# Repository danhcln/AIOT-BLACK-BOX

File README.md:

# AIoT Smart Black Box for Electric Motorcycles

> **Tên đề tài**: Thiết kế hộp đen AIoT thông minh phân tích và ghi lại sự cố xe máy điện  
> **Tác giả**: Nguyễn Lê Công Danh (danhcln)  
> **Ngành**: Kỹ thuật Điện - Điện tử / IoT & Hệ thống nhúng  
> **Nền tảng vi điều khiển**: Espressif ESP32-S3 (N16R8)  
> **Công cụ thiết kế EDA**: KiCad v8 / v9  
> **Trạng thái phần cứng**: Đã hoàn thiện thiết kế mạch in PCB 1 lớp đồng `B.Cu` (Nghiệm thu GATE 3.2 - 0 lỗi ERC/DRC)

---

## 1. Giới thiệu dự án (Project Introduction)

Hộp đen AIoT (Event Data Recorder - EDR) cho xe máy điện là một thiết bị thông minh gắn trên phương tiện hai bánh nhằm liên tục giám sát trạng thái động học, phát hiện các tình huống tai nạn, va chạm, đổ ngã và tự động gửi cảnh báo khẩn cấp (kèm tọa độ định vị GPS toàn cầu) về người thân/cứu hộ thông qua mạng viễn thông 4G LTE.

Đồng thời, toàn bộ dữ liệu cảm biến (gia tốc 3 trục, vận tốc góc, vận tốc di chuyển, thời gian thực và trạng thái hệ thống) được ghi liên tục với tần số cao vào thẻ nhớ MicroSD theo định dạng hộp đen tiêu chuẩn, phục vụ công tác điều tra nguyên nhân tai nạn và phân tích hành vi lái xe.

```
+---------------------------------------------------------------------------------------------------+
|                                 HỆ THỐNG HỘP ĐEN AIoT XE MÁY ĐIỆN                                 |
+---------------------------------------------------------------------------------------------------+
|  [CẢM BIẾN & ĐỘNG HỌC]    [ĐỊNH VỊ & VIỄN THÔNG]     [LƯU TRỮ & HIỂN THỊ]    [NGUỒN & AN TOÀN]    |
|   - MPU6050 (Gia tốc/Góc)  - NEO-M8N (GPS/GNSS)       - MicroSD (SPI Logger)  - UPS LX-2BUPS (5V) |
|   - DS3231 (Thời gian RTC) - A7680C (4G LTE / SMS)    - OLED 0.96" (SSD1306)  - Pin 18650 Li-ion  |
|                                                                               - Còi 5V & Nút Hủy  |
+---------------------------------------------------------------------------------------------------+
                                                  |
                                                  v
                               +-------------------------------------+
                               |   VI ĐIỀU KHIỂN TRUNG TÂM ESP32-S3  |
                               |    Dual-Core Xtensa LX7 @ 240MHz    |
                               |    16MB Flash + 8MB Octal PSRAM     |
                               +-------------------------------------+
```

---

## 2. Mục tiêu hệ thống (System Objectives)

1. **Giám sát động học thời gian thực**: Đo lường gia tốc 3 trục ($A_x, A_y, A_z$) và vận tốc góc ($\omega_x, \omega_y, \omega_z$) để phát hiện tức thời trạng thái ngã xe (nghiêng $> 60^\circ$) hoặc va chạm mạnh ($> 3G$).
2. **Định vị toàn cầu chính xác**: Cập nhật tọa độ kinh độ, vĩ độ, độ cao và tốc độ di chuyển từ vệ tinh GPS/GLONASS với chu kỳ 10Hz.
3. **Cảnh báo cứu nạn tự động qua SMS 4G**: Khi xảy ra sự cố, hệ thống đếm ngược 10 giây (kèm còi báo động). Nếu người lái không bấm nút hủy (CANCEL), hệ thống lập tức soạn tin nhắn SMS chứa link Google Maps chính xác gửi tới số điện thoại khẩn cấp.
4. **Ghi nhật ký hộp đen liên tục**: Lưu trữ dữ liệu cảm biến dạng CSV vào thẻ nhớ MicroSD (chu kỳ 100ms/mẫu) với nhãn thời gian thực chính xác đến từng giây từ RTC DS3231.
5. **Giao diện trực quan**: Hiển thị tốc độ xe, trạng thái kết nối GPS, sóng 4G, góc nghiêng và thời gian thực trên màn hình OLED 0.96 inch.
6. **Nguồn điện độc lập, tin cậy**: Sử dụng mạch quản lý sạc/xả thông minh UPS 2 cell 18650, tự động duy trì hoạt động khi ắc quy chính của xe bị ngắt nguồn do va chạm.
7. **Thiết kế phần cứng tối ưu chi phí**: Bo mạch Carrier Board được thiết kế hoàn hảo trên **PCB 1 lớp đồng `B.Cu`**, sử dụng các jumper dây cách điện chuẩn hóa, dễ dàng gia công và hàn thủ công trong điều kiện phòng thí nghiệm tại Việt Nam.

---

## 3. Sơ đồ khối tổng quan (System Architecture)

```
                       +-----------------------------+
                       |   Ắc quy xe / Nguồn USB-C   |
                       +-----------------------------+
                                      |
                                      v
                       +-----------------------------+
                       |    MẠCH NGUỒN LX-2BUPS      |
                       |  (Pin 18650 + Sạc + Boost)  |
                       +-----------------------------+
                                      |
                                      +------------------+
                                      | 5V_SYS (Tải 3A)   |
                                      v                  v
                             +-----------------+  +-----------------+
                             | BUCK MINI-360   |  |   A7680C 4G     |
                             | (5V -> 3V3_SYS) |  | (Đỉnh dòng 2A)  |
                             +-----------------+  +-----------------+
                                      |
       +------------------------------+------------------------------+
       |                              |                              |
       v                              v                              v
+---------------+             +---------------+             +-----------------+
| MPU-6050      |             | DS3231 RTC    |             | OLED 0.96"      |
| I2C: 0x69     |             | I2C: 0x68     |             | I2C: 0x3C       |
+---------------+             +---------------+             +-----------------+
       |                              |                              |
       +------------------------------+------------------------------+
                                      |
                                  Bus I2C (SDA: GPIO8 | SCL: GPIO9)
                                      |
                                      v
                       +-----------------------------+
                       |   ESP32-S3 DEVKITC-1 N16R8  |
                       +-----------------------------+
                        |      |        |          |
      Bus SPI (MOSI:11  |      |        |          |
               MISO:13  |      |        |          | UART (TX:17 | RX:18)
               SCK:12   |      |        |          +---------------------> NEO-M8N GPS
               CS:10)   |      |        |
                        v      |        | UART (TX:16 | RX:15)
                 MicroSD Card  |        +---------------------> SIM A7680C 4G
                               |
                               +------------------------------> Nút CANCEL (GPIO6)
                               |
                               +------------------------------> Còi báo (GPIO5) & LED (GPIO7)
```

---

## 4. Các linh kiện chính & Bảng bóc tách vật tư (BOM)

Toàn bộ các linh kiện trong hệ thống đã được kiểm toán thực tế và khóa mã trong bảng bóc tách vật tư [`BOM_MAINBOARD_REV1.csv`](./PCB_AIOT_BLACKBOX/AIOT_BLACKBOX_MAINBOARD_REV1/BOM_MAINBOARD_REV1.csv):

| TT | Ký hiệu (RefDes) | Tên linh kiện / Module | Thông số kỹ thuật | Giao tiếp / Chân ESP32-S3 | Ghi chú & Vai trò |
|---|---|---|---|---|---|
| 1 | **U1** | ESP32-S3-DevKitC-1 N16R8 | Dual-Core 240MHz, 16MB Flash, 8MB PSRAM | Bo mạch trung tâm | Điều khiển toàn bộ hệ thống |
| 2 | **U2** | MPU-6050 (GY-521) | Con quay hồi chuyển & Gia tốc kế 6-DOF | I2C (SDA: 8, SCL: 9) | Chân AD0 nối 3V3 $\rightarrow$ Địa chỉ `0x69` |
| 3 | **U3** | DS3231 (ZS-042) | Real-Time Clock có bù nhiệt độ TCXO | I2C (SDA: 8, SCL: 9) | Địa chỉ `0x68` (Đã gỡ bỏ trở sạc R5) |
| 4 | **U4** | NEO-M8N GNSS Module | 72 kênh định vị đa vệ tinh (GPS/GLONASS) | UART (TX: 17, RX: 18) | Baudrate 9600 bps, chu kỳ 10Hz |
| 5 | **U5** | A7680C 4G LTE Breakout | LTE Cat-1 hỗ trợ SMS, TCP/IP, VoLTE | UART (TX: 16, RX: 15) | Baudrate 115200 bps, cấp nguồn hình sao |
| 6 | **J1** | MicroSD Card Adapter | Chuẩn SPI có đệm logic và IC ổn áp 3.3V | SPI (CS: 10, MOSI: 11, SCK: 12, MISO: 13) | Định dạng FAT32, ghi log sự cố liên tục |
| 7 | **U7** | OLED 0.96 inch | 128x64 điểm ảnh, Driver SSD1306 | I2C (SDA: 8, SCL: 9) | Địa chỉ `0x3C`, hiển thị trạng thái |
| 8 | **U6** | Module Buck 3.3V (Mini-360) | Hạ áp xung DC-DC 5V $\rightarrow$ 3.3V / 2A | Nguồn hệ thống | Cung cấp nguồn riêng `3V3_SYS` |
| 9 | **J2** | Module UPS LX-2BUPS | Mạch sạc/xả dự phòng 2 cell 18650, ra 5V/3A | Nguồn tổng `5V_SYS` | Cấp nguồn chính không gián đoạn |
| 10 | **BZ1** | Còi báo chủ động (Active Buzzer) | 5V Piezoelectric Audio Indicator | Điều khiển qua Q1 (GPIO5) | Kêu cảnh báo trước khi phát tín hiệu SOS |
| 11 | **SW1** | Nút bấm hủy cảnh báo (CANCEL) | Nút nhấn nhả THT kèm tụ chống dội 100nF | GPIO6 (Kéo lên $10\text{k}\Omega$) | Hủy phát SMS khẩn cấp trong 10 giây |
| 12 | **D1** | LED báo trạng thái 5mm | LED siêu sáng màu xanh lá kèm trở $330\Omega$ | GPIO7 | Nhấp nháy báo hệ thống hoạt động |
| 13 | **NT1** | Net-Tie hình sao nguồn SIM | Đường đồng liền `B.Cu` rộng 2.5mm | Nối `5V_SYS` $\rightarrow$ `SIM_PWR` | Ngăn sụt áp lan truyền khi phát sóng 4G |
| 14 | **JMP1..11**| 11 Wire Jumper mặt trên | Dây đồng 22/24 AWG bọc cách điện Teflon/PVC | Cắm xuyên lỗ xuống `B.Cu` | Xử lý các đường giao cắt trên PCB 1 lớp |

---

## 5. ESP32-S3 và Firmware (`filecodemain.cpp`)

Toàn bộ logic hoạt động được lập trình tối ưu trong file firmware duy nhất: [`filecodemain.cpp`](./filecodemain.cpp).

### Bản đồ phân bổ chân phần cứng (GPIO Mapping Locked)
```cpp
// 1. I2C Bus (OLED, RTC DS3231, IMU MPU6050)
#define I2C_SDA_PIN         8
#define I2C_SCL_PIN         9

// 2. SPI Bus (MicroSD Card Adapter)
#define SD_CS_PIN          10
#define SPI_MOSI_PIN       11
#define SPI_SCK_PIN        12
#define SPI_MISO_PIN       13

// 3. UART Hardware (Module 4G LTE A7680C)
#define SIM_TX_PIN         16   // ESP32 TX -> SIM RX
#define SIM_RX_PIN         15   // ESP32 RX -> SIM TX

// 4. UART Hardware (Module GPS NEO-M8N)
#define GPS_TX_PIN         17   // ESP32 TX -> GPS RX
#define GPS_RX_PIN         18   // ESP32 RX -> GPS TX

// 5. Điều khiển ngoại vi và an toàn
#define BUZZER_PIN          5   // Điều khiển cực Base transistor Q1
#define CANCEL_BTN_PIN      6   // Nút bấm hủy gửi SMS (kéo lên nội trở + R3)
#define LED_STATUS_PIN      7   // LED nhấp nháy chỉ báo trạng thái
```

### Thuật toán vận hành cốt lõi
1. **Khởi tạo (Setup)**:
   - Khởi tạo cổng nạp Serial (115200 bps).
   - Thiết lập I2C Bus tại tần số chuẩn 100kHz.
   - Quét bus I2C và khởi tạo OLED (`0x3C`), DS3231 (`0x68`), MPU6050 (`0x69`).
   - Cấu hình dải đo MPU6050 $\pm 16G$, bộ lọc thông thấp số $21\text{Hz}$.
   - Khởi tạo SPI và mount phân vùng thẻ nhớ MicroSD. Tạo file nhật ký `blackbox_YYYYMMDD.csv` nếu chưa có.
   - Khởi động UART1 (GPS) và UART2 (SIM 4G). Đồng bộ tập lệnh AT cho module SIM.
2. **Vòng lặp chính (Loop - Non-blocking State Machine)**:
   - **Tần số 10Hz (100ms)**: Đọc dữ liệu gia tốc và góc nghiêng từ MPU6050; đọc câu tin NMEA từ GPS. Ghi một dòng log vào thẻ nhớ:
     `Timestamp, AccX, AccY, AccZ, GyroX, GyroY, GyroZ, Lat, Lon, Speed, Status`
   - **Xử lý tai nạn**: Nếu góc nghiêng $|Angle| > 60^\circ$ hoặc $|Acc| > 3.0G$, hệ thống chuyển sang trạng thái `ACCIDENT_TRIGGERED`.
   - **Đếm ngược cứu hộ**: Bật còi BZ1 kêu bíp liên tục trong 10 giây. Nếu trong thời gian này người lái bấm nút CANCEL (GPIO6), hệ thống hủy lệnh và quay về bình thường.
   - **Gửi tin nhắn SOS**: Hết 10 giây, module A7680C kích hoạt lệnh `AT+CMGS`, gửi tin nhắn SMS chứa link Google Maps:
     `[EDR VI TRI XE] https://maps.google.com/?q=<Latitude>,<Longitude>`
   - **Cập nhật màn hình OLED (500ms)**: Hiển thị tọa độ, tốc độ, dung lượng thẻ nhớ và trạng thái kết nối.

> **Lưu ý bảo mật**: Trong bản chia sẻ công khai trên GitHub, số điện thoại khẩn cấp `DEFAULT_PHONE` được thay bằng giá trị placeholder `09xxxxxxxx`. Người triển khai thực tế chỉ cần thay bằng số điện thoại của người thân.

---

## 6. MPU6050 – Phát hiện chuyển động bất thường

- **Địa chỉ phần cứng I2C**: Được khóa cứng ở mức `0x69` bằng cách cấp nguồn `3V3_SYS` vào chân **AD0** (thông qua jumper `JMP8`). Điều này ngăn ngừa hoàn toàn hiện tượng xung đột địa chỉ với RTC DS3231 (`0x68`).
- **Xử lý tín hiệu**: Firmware sử dụng bộ lọc số thông thấp DLPF $21\text{Hz}$ để triệt tiêu dao động rung cơ học từ mặt đường và động cơ xe máy điện, chỉ bắt các xung gia tốc thực của va chạm.
- **Quy chuẩn bố trí trên PCB**: Module MPU6050 được đặt tại tâm trọng lực bo mạch (Zone 4), cách xa còi báo động tối thiểu 40mm để chống nhiễu sóng âm và từ trường.

---

## 7. GPS NEO-M8N – Định vị toàn cầu

- **Độ nhạy & Băng tần**: Hỗ trợ đồng thời hệ thống định vị GPS của Mỹ và GLONASS của Nga. Tốc độ cập nhật 10Hz, độ chính xác vị trí $< 2.5\text{m}$.
- **Bảo toàn tín hiệu**: Giao tiếp qua UART phần cứng (GPIO17 / GPIO18) với baudrate 9600 bps. Pin dự phòng trên module giúp duy trì dữ liệu ephemeris vệ tinh (Hot Start $< 1\text{s}$).

---

## 8. SIM A7680C – Viễn thông 4G LTE & Gửi SMS

- **Băng tần mạng**: Hỗ trợ 4G LTE Cat-1 (B1/B3/B5/B8/B34/B38/B39/B40/B41) tương thích hoàn toàn với tất cả nhà mạng tại Việt Nam (Viettel, Vinaphone, Mobifone).
- **Chống sụt áp phát sóng**: Module 4G tiêu thụ dòng đỉnh lên tới $2\text{A}$ trong thời gian ngắn (xung phát RF 577µs). Mạch in được trang bị nhánh nguồn hình sao `SIM_PWR` rộng 2.5mm đi qua Net-Tie `NT1` cùng cặp tụ lọc Low-ESR $470\mu\text{F}$ và $100\text{nF}$ đặt sát chân cấp nguồn module.

---

## 9. RTC DS3231 – Thời gian thực chính xác cao

- **Độ chính xác**: Sử dụng thạch anh tích hợp có bù nhiệt độ (TCXO), sai số cực thấp $< \pm 2\text{ppm}$ ($< 1$ phút mỗi năm).
- **An toàn pin**: Đã gỡ bỏ điện trở sạc R5 trên module ZS-042 để sử dụng an toàn với pin cúc áo thông thường CR2032 không sạc, loại bỏ triệt để nguy cơ phồng nổ pin.

---

## 10. MicroSD – Ghi dữ liệu hộp đen

- Giao tiếp qua bus SPI tốc độ cao. Dữ liệu được ghi theo khối nhị phân và đóng gói định dạng CSV tiêu chuẩn.
- Tự động kiểm tra tính toàn vẹn của thẻ nhớ khi khởi động; chỉ thị cảnh báo lỗi lên OLED nếu thẻ chưa được cắm hoặc hỏng định dạng.

---

## 11. OLED 0.96 inch – Màn hình hiển thị

- Sử dụng màn hình OLED công nghệ SSD1306 độ phân giải 128x64 điểm ảnh, giao tiếp I2C 2 dây.
- Hiển thị trực quan tốc độ di chuyển hiện tại, số lượng vệ tinh GPS kết nối, trạng thái sóng 4G, góc nghiêng thời gian thực và thời gian ngày/giờ.

---

## 12. Khối nguồn thông minh UPS LX-2BUPS

- **Nguồn cấp chính**: 2 cell pin Lithium-ion 18650 mắc song song, tích hợp IC quản lý sạc/xả thông minh và mạch boost DC-DC đồng bộ cho ra điện áp ổn định $5\text{V} / 3\text{A}$ (`5V_SYS`).
- **Nguồn sạc ngoài**: Cổng USB-C / VBUS hỗ trợ sạc điện tự động khi cắm sạc ngoài.
- **Nguồn thứ cấp**: Module Buck xung Mini-360 hạ áp từ `5V_SYS` xuống `3V3_SYS` cấp riêng cho khối logic cảm biến, tuyệt đối không dùng nguồn từ chân 3.3V của ESP32 để nuôi ngoại vi.

---

## 13. Bản vẽ Schematic KiCad

Hệ thống được thiết kế hoàn chỉnh trên KiCad EDA với đầy đủ các dự án nguyên lý:
1. **Schematic hệ thống chính**: Nằm tại [`PCB_AIOT_BLACKBOX/AIOT_BLACKBOX_MAINBOARD_REV1/AIOT_BLACKBOX_MAINBOARD_REV1.kicad_sch`](./PCB_AIOT_BLACKBOX/AIOT_BLACKBOX_MAINBOARD_REV1/AIOT_BLACKBOX_MAINBOARD_REV1.kicad_sch).
2. **Schematic báo cáo & thuyết minh chuẩn A4 Landscape**: Nằm tại [`Schematic_Thay/AIOT_BLACKBOX_PRESENTATION/AIOT_BLACKBOX_PRESENTATION.kicad_sch`](./Schematic_Thay/AIOT_BLACKBOX_PRESENTATION/AIOT_BLACKBOX_PRESENTATION.kicad_sch).
3. **Schematic chuyên sâu khối nguồn**: Nằm tại [`THIET_KE_KHOI_NGUON/AIOT_BLACKBOX_POWER_SUPPLY.kicad_sch`](./THIET_KE_KHOI_NGUON/AIOT_BLACKBOX_POWER_SUPPLY.kicad_sch).

---

## 14. Thiết kế PCB một lớp đồng `B.Cu` & 11 Wire Jumper

Nhằm phục vụ chế tạo thủ công trong phòng thí nghiệm (phương pháp ủi phim nhiệt, rửa mạch hóa chất $\text{FeCl}_3$ hoặc phay cơ CNC PCB 1 mặt), bo mạch được thiết kế theo các nguyên tắc nghiêm ngặt:
- **Chỉ 1 lớp đồng dẫn điện**: Toàn bộ đường mạch đồng, pad hàn và mặt phẳng mass GND đều nằm độc quyền trên lớp đáy **`B.Cu`**.
- **Không sử dụng Via**: Tuyệt đối không có via xuyên bo, loại bỏ hoàn toàn công đoạn gia công mạ lỗ phức tạp.
- **Giải quyết giao cắt bằng 11 Jumper dây cách điện**: Các đường tín hiệu logic bị giao cắt được xử lý bằng 11 cầu nhảy dây đồng lõi đơn (Teflon/PVC) cắm mặt trên (`Top`) và hàn vào các pad THT chuyên dụng.

### Bảng thông số kỹ thuật 11 Jumper dây (REV3)
| Jumper | Pitch (mm) | Net kết nối | Vai trò kỹ thuật |
|---|---|---|---|
| **`JMP1`** | 12.70 mm | `Net-(J1-MOSI)` | Nhảy tín hiệu SPI MOSI qua SCK và MISO vào ESP32 Pin 17 |
| **`JMP2`** | 7.62 mm | `3V3_SYS` | Nhảy nguồn 3V3_SYS qua đường SIM_PWR (2.5mm) cấp R3 nút bấm |
| **`JMP3`** | 7.62 mm | `Net-(U1-GPIO6)` | Nhảy tín hiệu CANCEL qua chân Base Q1 còi báo động vào ESP32 Pin 6 |
| **`JMP4`** | 10.16 mm | `/I2C_SDA_GPIO8` | Nhảy bus dữ liệu I2C_SDA qua đường ngang SCL (Y=91.50) |
| **`JMP5`** | 7.62 mm | `Net-(U1-GPIO6)` | Nhảy tín hiệu CANCEL qua xương nguồn 5V_SYS (Y=43.50) |
| **`JMP6`** | 10.16 mm | `Net-(J1-MISO)` | Nhảy tín hiệu SPI MISO qua chân 5V và GND của header MicroSD J1 |
| **`JMP7`** | 10.16 mm | `3V3_SYS` | Nhảy nguồn 3V3_SYS qua SCL cấp cho RTC DS3231 và IMU MPU6050 |
| **`JMP8`** | 12.70 mm | `3V3_SYS` | Nhảy 3V3_SYS cấp AD0 MPU6050 để khóa cứng địa chỉ I2C `0x69` |
| **`JMP9`** | 7.62 mm | `3V3_SYS` | Nhảy 3V3_SYS cấp trở kéo lên R_PU2 ($4.7\text{k}\Omega$) cho bus SCL |
| **`JMP10`** | 7.62 mm | `/I2C_SCL_GPIO9` | Nhảy xung I2C_SCL qua sống ngang SDA (Y=104.00) cấp màn hình OLED |
| **`JMP11`** | 12.70 mm | `GND` | Nhảy mass GND MicroSD J1.6 qua sống 5V_SYS vào mặt phẳng mass GND |

---

## 15. Hình ảnh phần cứng & Bản vẽ PCB (Gallery)

Các bản vẽ độ phân giải cao 300 DPI phục vụ chế tạo và lắp ráp được lưu trữ tại thư mục [`PCB_AIOT_BLACKBOX/AIOT_BLACKBOX_MAINBOARD_REV1/GATE_3_ROUTING/`](./PCB_AIOT_BLACKBOX/AIOT_BLACKBOX_MAINBOARD_REV1/GATE_3_ROUTING/):

- **Bản vẽ mặt đồng đáy (B.Cu Mirrored)**: [`PCB_ROUTING_BOTTOM_COPPER_ONLY_REV3.png`](./PCB_AIOT_BLACKBOX/AIOT_BLACKBOX_MAINBOARD_REV1/GATE_3_ROUTING/PCB_ROUTING_BOTTOM_COPPER_ONLY_REV3.png) – Bản vẽ soi gương sẵn sàng in phim rửa mạch.
- **Bản vẽ lắp ráp & Jumper mặt trên (Top Assembly)**: [`PCB_ROUTING_TOP_JUMPERS_REV3.png`](./PCB_AIOT_BLACKBOX/AIOT_BLACKBOX_MAINBOARD_REV1/GATE_3_ROUTING/PCB_ROUTING_TOP_JUMPERS_REV3.png) – Hướng dẫn chi tiết vị trí và màu sắc dây jumper.
- **Bản vẽ bố trí linh kiện tổng thể (Top Placement)**: [`PCB_PLACEMENT_TOP_REV2.png`](./PCB_AIOT_BLACKBOX/AIOT_BLACKBOX_MAINBOARD_REV1/GATE_2_PLACEMENT/PCB_PLACEMENT_TOP_REV2.png).
- **Hình ảnh linh kiện module thực tế**: Lưu trữ trong thư mục [`Hình ảnh linh kiện/`](./Hình%20ảnh%20linh%20kiện/).

---

## 16. Cấu trúc thư mục Repository & Hướng dẫn tra cứu (Navigation Guide)

```
AIOT-BLACK-BOX/
├── .agents/                                # Quy tắc thiết kế và skill của hệ thống Antigravity
│   ├── rules/                              # PCB_DESIGN_RULES_AIOT.md và quy tắc an toàn
│   └── skills/                             # Các công cụ kiểm toán, xác minh và sửa lỗi
├── Bao_Cao/                                # Báo cáo đồ án định dạng Word (.docx) và PDF
├── DATASHEET_LINH_KIEN/                    # Chỉ mục tra cứu thông số kỹ thuật và link chính hãng
│   ├── DATASHEET_INDEX.csv                 # Bảng tra cứu CSV 30 tài liệu sản xuất
│   ├── DATASHEET_INDEX.xlsx                # Bảng tính Excel định dạng màu
│   └── README.md                           # Hướng dẫn và link tải trực tiếp từ nhà sản xuất
├── Hình ảnh linh kiện/                     # Thư viện ảnh chụp thực tế hai mặt của các module
├── Mẫu của thầy/                           # Biểu mẫu, nhật ký và sơ đồ khối mẫu từ giảng viên
├── PCB_AIOT_BLACKBOX/                      # Dự án thiết kế mạch in PCB KiCad
│   └── AIOT_BLACKBOX_MAINBOARD_REV1/       # Project PCB chính thức của hệ thống
│       ├── AIOT_Blackbox_Local.pretty/     # Thư viện Footprint KiCad nội bộ dự án
│       ├── BOM_MAINBOARD_REV1.csv          # Bảng bóc tách vật tư 40 linh kiện (kèm 11 jumper)
│       ├── GATE_0_AUDIT/                   # Hồ sơ kiểm toán code, sơ đồ chân và công suất
│       ├── GATE_1_FOOTPRINT/               # Hồ sơ xác minh footprint và kích thước cơ khí
│       ├── GATE_2_PLACEMENT/               # Hồ sơ và hình ảnh định vị linh kiện chuẩn RF
│       ├── GATE_3_ROUTING/                 # Bản vẽ PCB hoàn thiện REV3 (Bottom & Top Jumpers)
│       ├── AIOT_BLACKBOX_MAINBOARD_REV1.kicad_pcb # File thiết kế mạch in KiCad PCB chính thức
│       ├── AIOT_BLACKBOX_MAINBOARD_REV1.kicad_sch # File nguyên lý kết nối bo mạch
│       └── fp-lib-table, sym-lib-table     # Cấu hình thư viện dự án
├── Schematic/                              # Thiết kế nguyên lý ban đầu
├── Schematic_Thay/                         # Thiết kế nguyên lý chuẩn hóa thuyết minh A4 Landscape
├── THIET_KE_KHOI_NGUON/                    # Dự án thiết kế và tính toán chi tiết khối nguồn
├── filecodemain.cpp                        # Firmware chính thức của ESP32-S3
├── SCHEMATIC_DRAWING_RULES.md              # Bộ quy chuẩn trình bày bản vẽ nguyên lý
├── BAO_GIA_LINH_KIEN_AIOT_SMART_BLACK_BOX.xlsx # Bảng báo giá linh kiện thị trường TP.HCM
├── .gitignore                              # Cấu hình loại bỏ file rác, file tạm và cache
└── README.md                               # Tài liệu giới thiệu tổng quan dự án (File này)
```

> **Lưu ý về thư viện KiCad**: Để đảm bảo tính độc lập và khả năng mở dự án trên mọi máy tính khác nhau mà không bị mất dấu thư viện, dự án sử dụng bảng ánh xạ thư viện cục bộ (`sym-lib-table` và `fp-lib-table`). Nếu mở trên máy mới, hãy giữ nguyên cấu trúc thư mục để KiCad tự động nhận diện biến môi trường `${KIPRJMOD}`.

---

## 17. Trạng thái phát triển hiện tại (Development Status)

- **Firmware**: Đã nạp và kiểm tra thành công trên phần cứng rời (ESP32-S3, OLED, MPU6050, DS3231, NEO-M8N, A7680C, MicroSD).
- **Schematic**: Đạt **0 Error, 0 Warning** khi chạy kiểm tra tự động `kicad-cli sch erc`.
- **PCB Carrier Board**: Đã hoàn thành nghiệm thu **GATE 3.2** trên bo mạch 1 lớp đồng `B.Cu` với 11 wire jumper, đạt **0 vi phạm chập mạch, 0 vi phạm khoảng cách cách điện, 0 vi phạm va chạm lỗ khoan và 0 đường dây giao cắt**.
- **Kế hoạch tiếp theo**: Tiến hành phân tích toàn vẹn nguồn điện tải nặng (GATE 4), chuẩn bị xuất Gerber và chế tạo mẫu thử nghiệm vật lý (GATE 5 & 6).

---

## 18. Các bước thử nghiệm & Hạn chế kỹ thuật (Testing & Limitations)

1. **Hạn chế của mạch in 1 lớp**: Việc sử dụng 11 wire jumper ở mặt trên là bắt buộc do định lý tô-pô mặt phẳng đối với các mạch có mật độ bus song song cao (I2C, SPI, UART). Người lắp ráp cần tuân thủ nghiêm ngặt bảng hướng dẫn chiều dài và cỡ dây trong file [`JUMPER_ASSEMBLY_REV3.csv`](./PCB_AIOT_BLACKBOX/AIOT_BLACKBOX_MAINBOARD_REV1/GATE_3_ROUTING/JUMPER_ASSEMBLY_REV3.csv).
2. **Yêu cầu đo kiểm trước khi cấp nguồn**: Do các lô linh kiện mua thực tế tại cửa hàng có thể có sự khác biệt về điện áp chân VCC của module SIM (3.8V hay 5V) hoặc thứ tự chân OLED (GND-VCC hay VCC-GND), bắt buộc phải dùng đồng hồ VOM đo kiểm tra thông mạch và điện áp tại các Test Point (`TP1`, `TP2`, `TP3`, `TP4`) trước khi cắm module vào socket.
3. **Môi trường hoạt động**: Thiết bị được thiết kế thử nghiệm trong môi trường xe máy điện tiêu chuẩn; khi đóng vỏ thực tế cần bổ sung đệm mút cao su chống sốc quanh cảm biến MPU6050 để giảm thiểu tối đa hiện tượng báo động giả do rung xóc cơ học.

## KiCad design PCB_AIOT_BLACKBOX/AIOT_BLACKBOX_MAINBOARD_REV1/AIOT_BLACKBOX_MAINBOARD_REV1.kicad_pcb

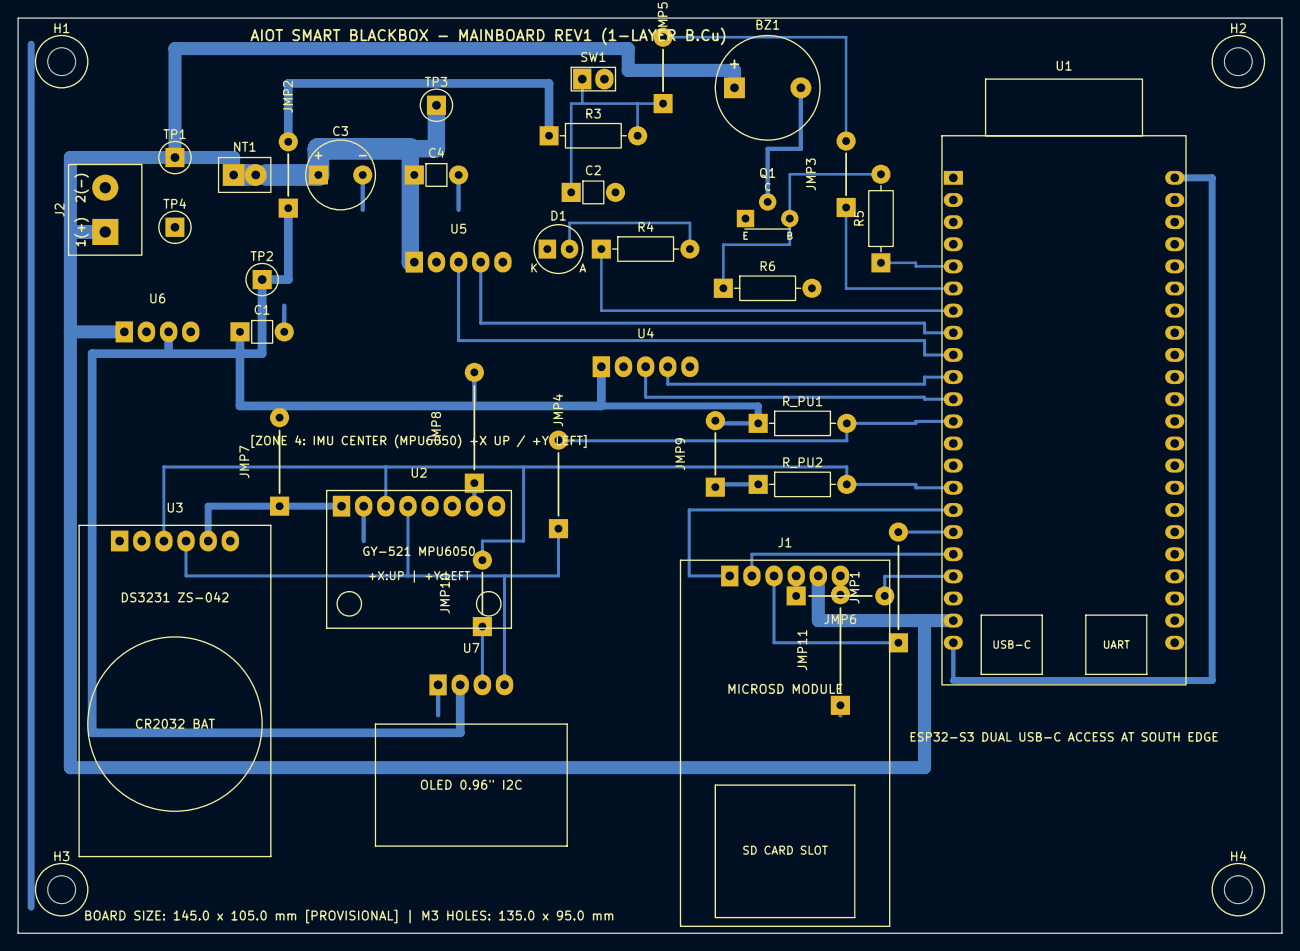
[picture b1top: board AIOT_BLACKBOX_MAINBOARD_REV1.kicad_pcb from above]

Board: 2 copper layers, 145.0 x 105.0 mm, 43 parts (0 on the bottom side), 20 nets.

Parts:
BZ1: BUZZER; Buzzer_D12.0mm_P7.62mm_SingleLayer
C1, C2, C4: 100nF; C_Disc_D5.0mm_P5.08mm_SingleLayer
C3: 470uF; CP_Radial_D8.0mm_P5.08mm_SingleLayer
D1: LED; LED_D5.0mm_P2.54mm_SingleLayer
H1, H2, H3, H4: M3_NPTH_PROVISIONAL; MountingHole_3.2mm_M3_NPTH
J1: MICROSD; Module_MicroSD_Adapter_1x06_P2.54mm_SingleLayer
J2: LX-2BUPS_5V_3A; TermBlock_1x02_P5.08mm_SingleLayer
JMP1, JMP8, JMP11: Wire_Jumper_12.70mm; WireJumper_P12.70mm_SingleLayer
JMP2, JMP3, JMP5, JMP9, JMP10: Wire_Jumper_7.62mm; WireJumper_P7.62mm_SingleLayer
JMP4, JMP6, JMP7: Wire_Jumper_10.16mm; WireJumper_P10.16mm_SingleLayer
NT1: STAR_5V_TO_SIM_PWR; NetTie_2_StarPoint_BCu_Width2.5mm
Q1: 2SC1815; TO-92_2SC1815_ECB_Staggered_SingleLayer
R3, R6: 10k; R_Axial_DIN0207_P10.16mm_SingleLayer
R4: 330R; R_Axial_DIN0207_P10.16mm_SingleLayer
R5: 1k; R_Axial_DIN0207_P10.16mm_SingleLayer
R_PU1, R_PU2: 4.7k; R_Axial_DIN0207_P10.16mm_SingleLayer
SW1: CANCEL; PinHeader_1x02_P2.54mm_SingleLayer
TP1: TP_5V; TestPoint_THTPad_D2.2mm_Drill1.0mm_SingleLayer
TP2: TP_3V3; TestPoint_THTPad_D2.2mm_Drill1.0mm_SingleLayer
TP3: TP_SIM_PWR; TestPoint_THTPad_D2.2mm_Drill1.0mm_SingleLayer
TP4: TP_GND; TestPoint_THTPad_D2.2mm_Drill1.0mm_SingleLayer
U1: ESP32-S3; ESP32_S3_N16R8_Socket_2x22_P2.54mm_Row25.40mm_SingleLayer
U2: MPU6050; Module_GY-521_MPU6050_1x08_P2.54mm_SingleLayer
U3: DS3231; Module_DS3231_ZS042_1x06_P2.54mm_SingleLayer
U4: NEO-M8N; Conn_GPS_NEO-M8N_V2149_1x05_P2.54mm_SingleLayer
U5: A7680C; Conn_SIM_Breakout_J6_1x05_P2.54mm_SingleLayer
U6: REG_3V3_MODULE; Conn_Regulator_3V3_1x04_P2.54mm_SingleLayer
U7: OLED 0.96"; OLED_0.96_GM009605v4.3_1x04_P2.54mm_SingleLayer

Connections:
3V3_SYS: C1.1, JMP2.1, JMP2.2, JMP7.1, JMP7.2, JMP8.1, JMP8.2, JMP9.1, JMP9.2, R3.1, R_PU1.1, R_PU2.1, TP2.1, U2.1, U2.7, U3.5, U4.1, U6.3, U7.2
5V_SYS: BZ1.1, J1.5, J2.1, NT1.1, TP1.1, U1.21, U6.1
/BUZZER_CTRL_GPIO5: R5.1, U1.5
/GPS_RX_GPIO18: U1.11, U4.3
/GPS_TX_GPIO17: U1.10, U4.4
/I2C_SCL_GPIO9: JMP10.1, JMP10.2, R_PU2.2, U1.15, U2.3, U3.3, U7.3
/I2C_SDA_GPIO8: JMP4.1, JMP4.2, R_PU1.2, U1.12, U2.4, U3.4, U7.4
/LED_STATUS_GPIO7: R4.1, U1.7
/SD_CS_GPIO10: J1.1, U1.16
/SIM_RX_GPIO15: U1.8, U5.4
/SIM_TX_GPIO16: U1.9, U5.3
GND: C1.2, C2.2, C3.2, C4.2, D1.1, J1.6, J2.2, JMP11.1, JMP11.2, Q1.1, R6.2, SW1.2, TP4.1, U1.22, U1.23, U2.2, U3.6, U4.2, U5.5, U6.2, U6.4, U7.1
unnamed: BZ1.2, Q1.2
unnamed: D1.2, R4.2
unnamed: J1.4, JMP6.1, JMP6.2, U1.19
unnamed: J1.3, JMP1.1, JMP1.2, U1.17
unnamed: J1.2, U1.18
unnamed: Q1.3, R5.2, R6.1
unnamed: C2.1, JMP3.1, JMP3.2, JMP5.1, JMP5.2, R3.2, SW1.1, U1.6
SIM_PWR: C3.1, C4.1, NT1.2, TP3.1, U5.1
